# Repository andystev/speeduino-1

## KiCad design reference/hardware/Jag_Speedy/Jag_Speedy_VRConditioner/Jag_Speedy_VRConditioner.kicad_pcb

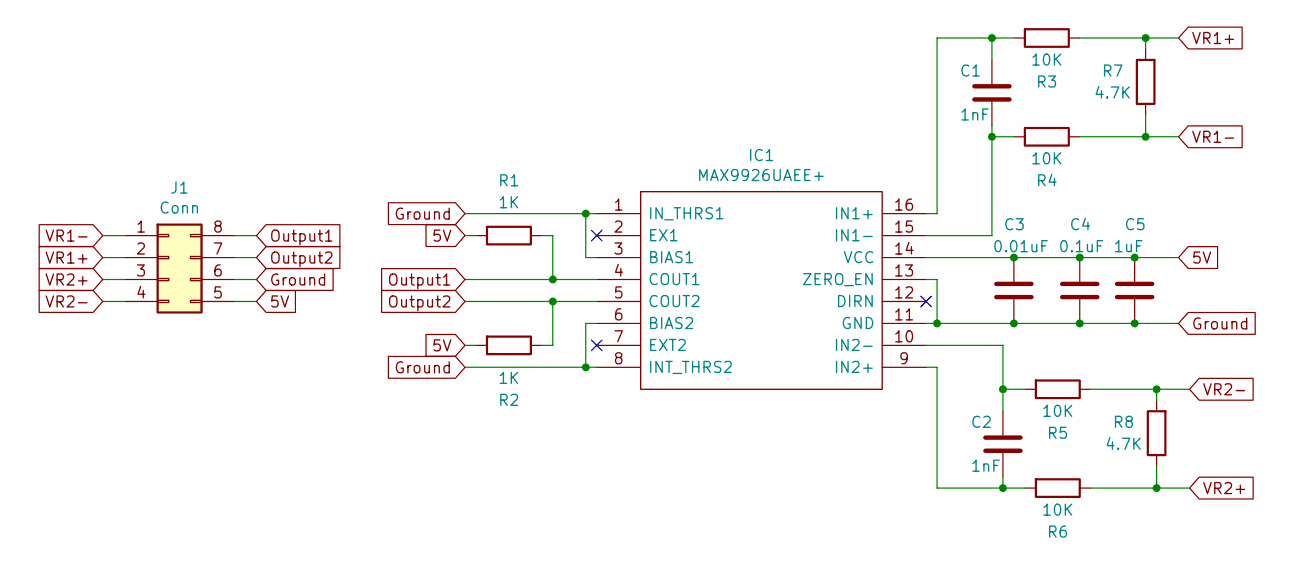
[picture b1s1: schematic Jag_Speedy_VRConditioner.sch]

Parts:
C1, C2: 1nF; C_0805_2012Metric
C3: 0.01uF; C_0805_2012Metric
C4: 0.1uF; C_0805_2012Metric
C5: 1uF; C_0805_2012Metric
IC1: MAX9926UAEE+; QSOP-16_3.9x4.9mm_P0.635mm; Manufacturer_Part_Number MAX9926UAEE+; Mouser Part Number 700-MAX9926UAEE
J1: Conn; DIP-8_W7.62mm_Socket
R1, R2: 1K; R_0805_2012Metric
R3, R4, R5, R6: 10K; R_0805_2012Metric
R7, R8: 4.7K; R_Axial_DIN0411_L9.9mm_D3.6mm_P12.70mm_Horizontal

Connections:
5V: C3.1, C4.1, C5.1, IC1.14 (VCC), J1.5, R1.2, R2.2
Ground: C3.2, C4.2, C5.2, IC1.1 (IN_THRS1), IC1.3 (BIAS1), IC1.6 (BIAS2), IC1.8 (INT_THRS2), IC1.11 (GND), IC1.13 (ZERO_EN), J1.6
unnamed: C1.1, IC1.16 (IN1+), R3.2
unnamed: C1.2, IC1.15 (IN1-), R4.2
unnamed: C2.1, IC1.10 (IN2-), R5.2
unnamed: C2.2, IC1.9 (IN2+), R6.2
Output1: IC1.4 (COUT1), J1.8, R1.1
Output2: IC1.5 (COUT2), J1.7, R2.1
VR1+: J1.2, R3.1, R7.2
VR1-: J1.1, R4.1, R7.1
VR2+: J1.3, R6.1, R8.1
VR2-: J1.4, R5.1, R8.2

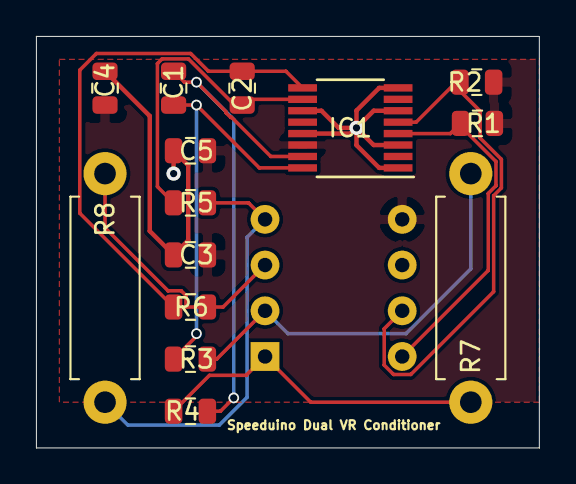
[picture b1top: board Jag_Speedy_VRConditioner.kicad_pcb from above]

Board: 2 copper layers, 27.9 x 22.9 mm, 15 parts (1 on the bottom side), 12 nets.

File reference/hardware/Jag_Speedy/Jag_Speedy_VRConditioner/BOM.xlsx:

QTY Full | Board Reference Full | Value | Type | Information | Manufacturer | Digikey Order | Model# | Digikey P/N | Order Qty | Digikey Price (GBP) | CTM Full Digikey | Order Price (GBP) | Note | Digikey import | General Description
 |  |  |  |  |  |  |  |  |  |  |  |  |  |  | x
2 | R1,R2 | 1k | RES SMD 1K OHM 1% 1/8W 0805 |  | Yageo | Y | RC0805FR-071KL | 311-1.00KCRCT-ND | 10 | 3.2000000000000001E-2 | 6.4000000000000001E-2 | 0.32 |  | 2,311-1.00KCRCT-ND | Resistor - 2x 1k
4 | R3,R4,R5,R6 | 10k | RES SMD 10K OHM 5% 1/8W 0805 |  | Yageo | Y | RC0805JR-0710KL | 311-10KARCT-ND | 20 | 2.7E-2 | 0.108 | 0.54 |  | 4,311-10KARCT-ND | Resistor - 4x 10k
2 | R7,R8 | 4.3k | RES 4.7K OHM 2W 5% AXIAL |  | Yageo | Y | FMP200JR-52-4K7 | 4.7KZCT-ND | 10 | 0.22600000000000001 | 0.45200000000000001 | 2.2600000000000002 |  | 2,4.7KZCT-ND | Resistor - 2x 4.3k
1 | C3 | 0.01uF | CAP CER 10000PF 50V X7R 0805 |  | Yageo | Y | CC0805KRX7R9BB103 | 311-1136-1-ND | 10 | 0.06 | 0.06 | 0.6 |  | 1,311-1136-1-ND | Capacitor - 1x 0.01uF
1 | C5 | 1uF | CAP CER 1UF 16V X7R 0805 |  | Yageo | Y | CC0805KKX7R7BB105 | 311-1365-1-ND | 10 | 0.10100000000000001 | 0.10100000000000001 | 1.01 |  | 1,311-1365-1-ND | Capacitor - 1x 1uF
2 | C1,C2 | 1nF | CAP CER 1000PF 50V X7R 0805 |  | Yageo | Y | CC0805KRX7R9BB102 | 311-1127-1-ND | 10 | 0.06 | 0.12 | 0.6 |  | 2,311-1127-1-ND | Capacitor - 2x 1nF
1 | C4 | 0.1uF | CAP CER 0.1UF 50V Y5V 0805 |  | Yageo | Y | CC0805ZRY5V9BB104 | 311-1361-1-ND | 10 | 0.06 | 0.06 | 0.6 |  | 1,311-1361-1-ND | Capacitor - 1x 0.1uF
 |  |  |  |  |  |  |  |  |  |  |  | 0
 |  |  |  |  |  |  |  |  |  |  |  | 0
1 | IC1 |  | IC SENSOR INTERFACE VARI 16-QSOP | 16-QSOP | Maxim Integrated | Y | MAX9926UAEE+T | MAX9926UAEE+TCT-ND | 5 | 4.32 | 4.32 | 21.6 |  | 1,MAX9926UAEE+TCT-ND | IC- 1x
2 | J1, | 0.100" | 4 Positions Header, Unshrouded, Breakaway Connector 0.100" (2.54mm) Through Hol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 | Pins for board | Harwin Inc | Y | M20-9990445 | 952-2265-ND | 10 | 0.27 | 0.54 | 2.7 |  | 2,952-2265-ND | Pins- 2x 0.100"
1 |  |  |  |  |  |  |  |  |  | 0 | 0 | 0
 |  |  |  |  |  |  | Total of Materials:Cost to Manufacture |  |  | GBP | 5.8250000000000002 | 30.23 | Not including shipping
 |  |  |  |  |  |  |  | Boards | 5 | 5.58 | 1.1160000000000001
 |  |  |  |  |  |  |  | Board Breakdown
 |  |  |  |  |  |  |  | Components + VAT |  |  | 6.99
 |  |  |  |  |  |  |  | Boards |  |  | 1.1160000000000001
 |  |  |  |  |  |  |  | Import Tax etc. |  |  | 0
 |  |  |  |  |  |  |  |  |  |  | 8.1059999999999999

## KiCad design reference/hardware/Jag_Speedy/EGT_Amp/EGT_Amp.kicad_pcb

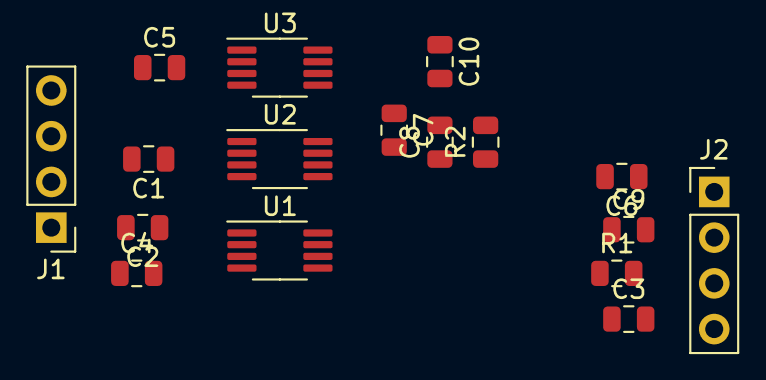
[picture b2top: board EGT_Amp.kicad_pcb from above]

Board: 2 copper layers, 17 parts (0 on the bottom side), 9 nets, no tracks yet.

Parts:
C1, C2, C3, C4, C5, C6, C7, C8, C9, C10: 0.1uF; C_0805_2012Metric
J1: Input; PinHeader_1x04_P2.54mm_Vertical
J2: Output; PinHeader_1x04_P2.54mm_Vertical
R1, R2: 1M; R_0805_2012Metric
U1, U2, U3: AD8495; MSOP-8_3x3mm_P0.65mm

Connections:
+InLeft: C2.2, C3.1, J1.1, R1.1, U1.8
+InRight: C7.2, C8.1, J1.3, R2.1, U2.8
-InLeft: C1.2, C2.1, J1.2, U1.1
-InRight: C6.2, C7.1, J1.4, U2.1
GND: C1.1, C3.2, C4.1, C4.2, C5.2, C6.1, C8.2, C9.1, C9.2, C10.2, J2.3, R1.2, R2.2, U1.2, U1.3, U2.2, U2.3, U3.1, U3.2, U3.3, U3.8
SignalOutAmbient: J2.1, U3.5, U3.6
SignalOutLeft: J2.4, U1.5, U1.6
SignalOutRight: U2.5, U2.6
VSS: C5.1, C10.1, J2.2, U1.7, U2.7, U3.7

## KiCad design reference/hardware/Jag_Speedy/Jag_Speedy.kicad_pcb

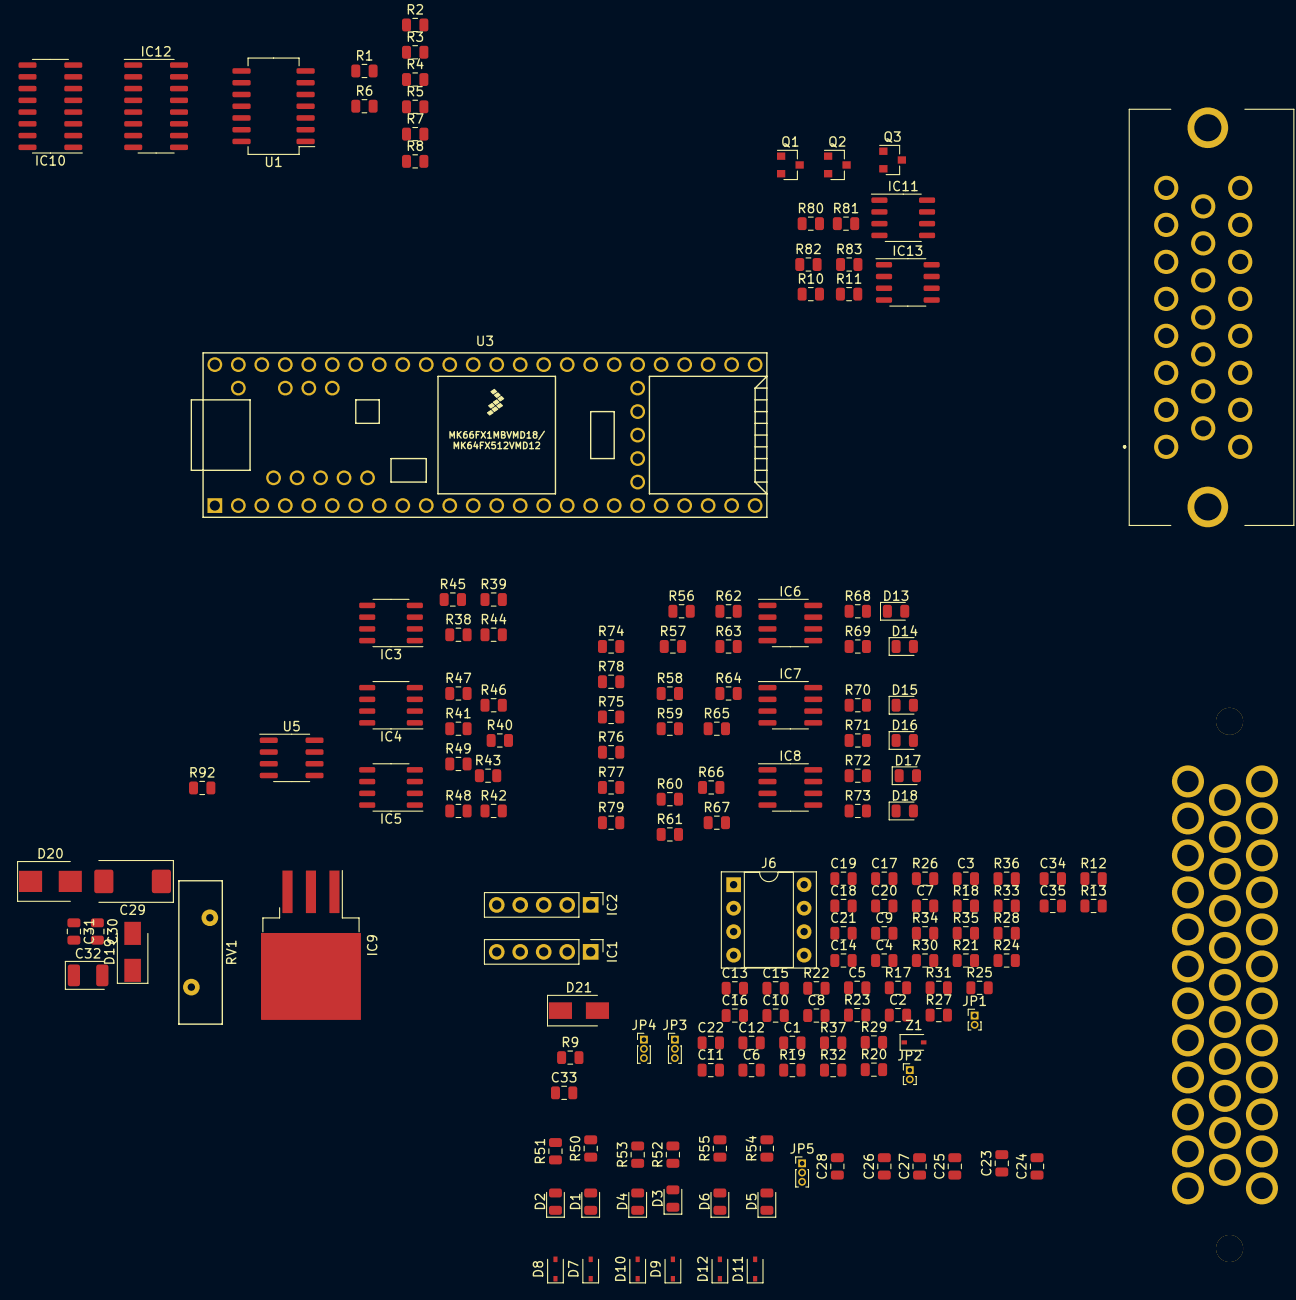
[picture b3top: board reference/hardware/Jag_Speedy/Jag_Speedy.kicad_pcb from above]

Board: 2 copper layers, 166 parts (0 on the bottom side), 132 nets, no tracks yet.

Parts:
C1, C9, C12, C13, C14, C15, C16, C23, C24, C25, C30, C31, C34: 0.1uF; C_0805_2012Metric
C2, C5, C11, C17, C18, C19, C20, C22, C35: 0.22uF; C_0805_2012Metric
C3, C7, C26, C27, C28: 1uF; C_0805_2012Metric
C4, C8: 0.3uF; C_0805_2012Metric
C6, C10, C21: 0.01uF; C_0805_2012Metric
C29: 10uF; CP_EIA-7343-31_Kemet-D
C32: 47uF; CP_EIA-3528-21_Kemet-B
C33: 4.7nF; C_0805_2012Metric
D1, D2, D3, D4, D5, D6, D13, D14, D15, D16, D17, D18: LED; LED_0805_2012Metric
D7, D8, D9, D10, D11, D12: 1N4004; D_SOD-323
D19, D21: 1N5818; D_SMA
D20: 1N5919BG; D_SMB
IC1, IC2: MPX4250AP; PinHeader_1x05_P2.54mm_Vertical
IC3, IC4, IC5, IC11, IC13: VNS3NV04DP-E; SO-8_3.9x4.9mm_P1.27mm
IC6, IC7, IC8: TC4424EPA; SOIC-8_3.9x4.9mm_P1.27mm
IC9: LM2940T-5.0_NOPB; TO-263-3_TabPin2
IC10, IC12: SP720APP; SOIC-16_3.9x9.9mm_P1.27mm
J1: 776087-1; 7760871
J2: 776163-1
J6: Dual VR Conditioner; DIP-8_W7.62mm_Socket
JP1, JP2: Pullup; PinHeader_1x02_P1.00mm_Vertical
JP3, JP4: VR Jumper; PinHeader_1x03_P1.00mm_Vertical
JP5: Ign Source Jumper; PinHeader_1x03_P1.00mm_Vertical
Q1, Q2, Q3: SSM3K357R,LF; SOT-23
R1, R2, R7, R8: 180k; R_0805_2012Metric
R3, R4, R5, R6: 330k; R_0805_2012Metric
R9, R92: 10K; R_0805_2012Metric
R10, R38, R39, R40, R41, R42, R43, R56, R57, R58, R59, R60, R61, R80, R81: 100k; R_0805_2012Metric
R11, R20, R28, R34, R35, R44, R45, R46, R47, R48, R49, R62, R63, R64, R65, R66, R67, R82, R83: 1k; R_0805_2012Metric
R12, R19, R23, R24, R25, R26, R68, R69, R70, R71, R72, R73: 2.49k; R_0805_2012Metric
R13, R18, R22, R29, R30, R31, R32, R33: 470; R_0805_2012Metric
R17, R21: 750; R_0805_2012Metric
R27: 3.9k; R_0805_2012Metric
R36, R37: 220R; R_0805_2012Metric
R50, R51, R52, R53, R54, R55: 680; R_0805_2012Metric
R74, R75, R76, R77, R78, R79: 10R; R_0805_2012Metric
RV1: ERZV14D220; RV_Disc_D15.5mm_W4.7mm_P7.5mm
U1: LMV324; SO-14_5.3x10.2mm_P1.27mm
U3: Teensy 3.5; Teensy35_36
U5: SN65HVD230; SOIC-8_3.9x4.9mm_P1.27mm
Z1: MM3Z5V1ST1G; D_SOD-323

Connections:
3V3: IC12.16, J1.20, J2.1, R12.1, R23.1, R24.1, R25.1, R26.1, U1.4, U3.15, U3.26, U5.3
5V: C3.1, C6.1, C7.1, C10.1, C31.1, C32.1, D20.1, D21.1, IC1.3, IC2.3, IC9.3, IC10.16, J1.11, J1.19, J2.18, J6.5, JP5.3, R9.1, R19.2, R34.2, R35.1, U3.53
12V: D19.2, J1.14, JP5.1, R27.1, R50.1, R51.1, R52.1, R53.1, R54.1, R55.1, RV1.1
ADCClamp01: C21.2, IC10.1, J6.8, R36.2, U3.50
ADCClamp02: C22.1, IC10.2, J6.7, R37.2, U3.33
ADCClamp03: C5.1, IC10.3, R7.2, R18.2
ADCClamp04: C11.1, IC10.4, R8.2, R22.2
ADCClamp05: IC12.1, R33.2, U3.45
ADCClamp06: C4.2, IC10.6, R1.1, R17.2
ADCClamp07: C8.2, IC10.7, R2.1, R21.2
ADCClamp08: C17.1, IC10.5, R29.2, U3.41
ADCClamp09: C18.1, IC12.9, R30.2, U3.42
ADCClamp10: C19.1, IC12.3, R31.2, U3.56
ADCClamp11: C20.1, C35.1, IC12.2, R13.2, R32.2, U3.47, U3.57
Barro-Signal-3.3V: U1.6, U1.7, U3.46
BluetoothRx: J1.22, U3.3
BluetoothTx: J1.23, U3.2
CAN-Rx: U3.6, U5.4
CAN-Tx: U3.5, U5.1
CANH: J1.15, U5.7
CANL: J1.16, U5.6
CCPump-OUT: IC11.5, J1.2
CCPump-Signal: R81.1, R83.1, U3.21
CLTSensor: C13.1, J2.8, R24.2, R30.1
CPU-A2: U1.8, U1.9, U3.43
CPU-A3: U1.13, U1.14, U3.44
CPU-A8: U1.1, U1.2, U3.49
CPU-D05: R80.2, R82.1, U3.7
CPU-D08: R38.2, R44.1, U3.10
CPU-D09: R39.1, R45.1, U3.11
CPU-D10: R40.1, R46.1, U3.12
CPU-D11: R41.1, R47.1, U3.13
CPU-D12: R42.2, R48.1, U3.14
CPU-D13: R43.1, R49.1, U3.40
CPU-D21: R59.1, R65.1, U3.48
CPU-D24: R20.2, U3.16, Z1.1
CPU-D25: C2.1, J2.2, R19.1, U3.17
CPU-D27: Q1.1, U3.19
CPU-D28: Q3.1, U3.20
CPU-D30: R10.2, R11.1, U3.22
CPU-D31: R58.2, R64.1, U3.23
CPU-D32: R60.2, R66.1, U3.24
CPU-D35: R61.1, R67.1, U3.32
CPU-D37: Q2.1, U3.34
CPU-D38: R57.1, R63.1, U3.35
CPU-D39: R56.2, R62.1, U3.36
CamSensor+: J2.16, JP2.2, JP4.2
CamSensor-: J2.17, J6.4
ClutchSwitch: J2.21, R20.1
CrankSensor+: J2.14, JP1.2, JP3.2
CrankSensor-: J2.15, J6.1
EGRSensor: C34.1, J2.12, R12.2, R13.1
Fan-OUT: J1.5, Q1.2
FuelPressureSensor: C14.1, J2.19, R25.2, R31.1
FuelPump-OUT: J1.4, Q2.2
IATSensor: C12.1, J2.6, R23.2, R29.1
IdlePWM-OUT: IC11.7, J1.6
Ign01-OUT: J2.29, R74.2
Ign02-OUT: J2.30, R75.2
Ign03-OUT: J2.31, R76.2
Ign04-OUT: J2.32, R77.2
Ign05-OUT: J2.33, R78.2
Ign06-OUT: J2.34, R79.2
IgnSourceV: C23.1, C24.1, C25.1, C26.1, C27.1, C28.1, IC6.6, IC7.6, IC8.6, JP5.2
Inj01-OUT: D7.1, IC3.7, J2.23
Inj02-OUT: D8.1, IC3.5, J2.24
Inj03-OUT: D9.1, IC4.7, J2.25
Inj04-OUT: D10.1, IC4.5, J2.26
Inj05-OUT: D11.1, IC5.7, J2.27
Inj06-OUT: D12.1, IC5.5, J2.28
unnamed: C16.1, R27.2, R28.1, R33.1
unnamed: C29.1, C30.1, D19.1, IC9.1
unnamed: D1.1, D7.2
unnamed: D1.2, R50.2
unnamed: D2.1, D8.2
unnamed: D2.2, R51.2
unnamed: D3.1, D9.2
unnamed: D3.2, R52.2
unnamed: D4.2, R53.2
unnamed: D5.2, R54.2
unnamed: D6.2, R55.2
unnamed: D4.1, D10.2
unnamed: D5.1, D11.2
unnamed: D6.1, D12.2
unnamed: D13.2, R68.1
unnamed: D14.2, R69.1
unnamed: D15.2, R70.1
unnamed: D16.2, R71.1
unnamed: D17.2, R72.1
unnamed: D18.2, R73.1
unnamed: IC1.1, R17.1
unnamed: IC2.1, R21.1
unnamed: IC3.2, R44.2
unnamed: IC3.4, R45.2
unnamed: IC4.2, R46.2
unnamed: IC4.4, R47.2
unnamed: IC5.2, R48.2
unnamed: IC5.4, R49.2
unnamed: IC6.2, R62.2
unnamed: IC6.4, R63.2
unnamed: IC6.5, R69.2, R75.1
unnamed: IC6.7, R68.2, R74.1
unnamed: IC7.2, R64.2
unnamed: IC7.4, R65.2
unnamed: IC7.5, R71.2, R77.1
unnamed: IC7.7, R70.2, R76.1
unnamed: IC8.2, R66.2
unnamed: IC8.4, R67.2
unnamed: IC8.5, R73.2, R79.1
unnamed: IC8.7, R72.2, R78.1
unnamed: IC11.2, R82.2
unnamed: IC11.4, R83.2
unnamed: IC13.2, R11.2
unnamed: J6.2, JP3.3
unnamed: J6.3, JP4.3
unnamed: JP1.1, R34.1
unnamed: JP2.1, R35.2
unnamed: JP3.1, R36.1
unnamed: JP4.1, R37.1
unnamed: R1.2, R4.1, U1.12
unnamed: R2.2, R3.1, U1.5
unnamed: R5.2, R7.1, U1.3
unnamed: R6.2, R8.1, U1.10
unnamed: R92.1, U5.8
O2Sensor: C1.1, J2.10, R18.1
OilPressureSensor: C15.1, J2.20, R26.2, R32.1
PowerGnd: C23.2, C24.2, C25.2, C26.2, C27.2, C28.2, C29.2, C30.2, C31.2, C32.2, C33.2, D13.1, D14.1, D15.1, D16.1, D17.1, D18.1, D20.2, IC3.1, IC3.3, IC4.1, IC4.3, IC5.1, IC5.3, IC6.3, IC7.3, IC8.3, IC9.2, IC10.8, IC11.1, IC11.3, IC12.8, IC13.1, IC13.3, J1.3, J1.9, J1.10, J1.17, J1.18, J1.21, J2.3, J2.5, J2.7, J2.9, J2.11, J2.13, J2.22, J2.35, Q1.3, Q2.3, Q3.3, R3.2, R4.2, R5.1, R6.1, R10.1, R38.1, R39.2, R40.2, R41.2, R42.1, R43.2, R56.1, R57.2, R58.1, R59.2, R60.1, R61.2, R80.1, R81.2, R92.2, RV1.2, U1.11, U3.1, U3.27, U3.39, U3.52, U3.60, U3.61, U5.2
Reset: C33.1, D21.2, R9.2, U3.29
SensorGnd: C1.2, C2.2, C3.2, C4.1, C5.2, C6.2, C7.2, C8.1, C9.2, C10.2, C11.2, C12.2, C13.2, C14.2, C15.2, C16.2, C17.2, C18.2, C19.2, C20.2, C21.1, C22.2, C34.2, C35.2, IC1.2, IC2.2, J6.6, R28.2, Z1.2
TPSSensor: C9.1, J2.4, R22.1
Tacho-OUT: J1.8, Q3.2
WPPWM-OUT: IC13.7, J1.12

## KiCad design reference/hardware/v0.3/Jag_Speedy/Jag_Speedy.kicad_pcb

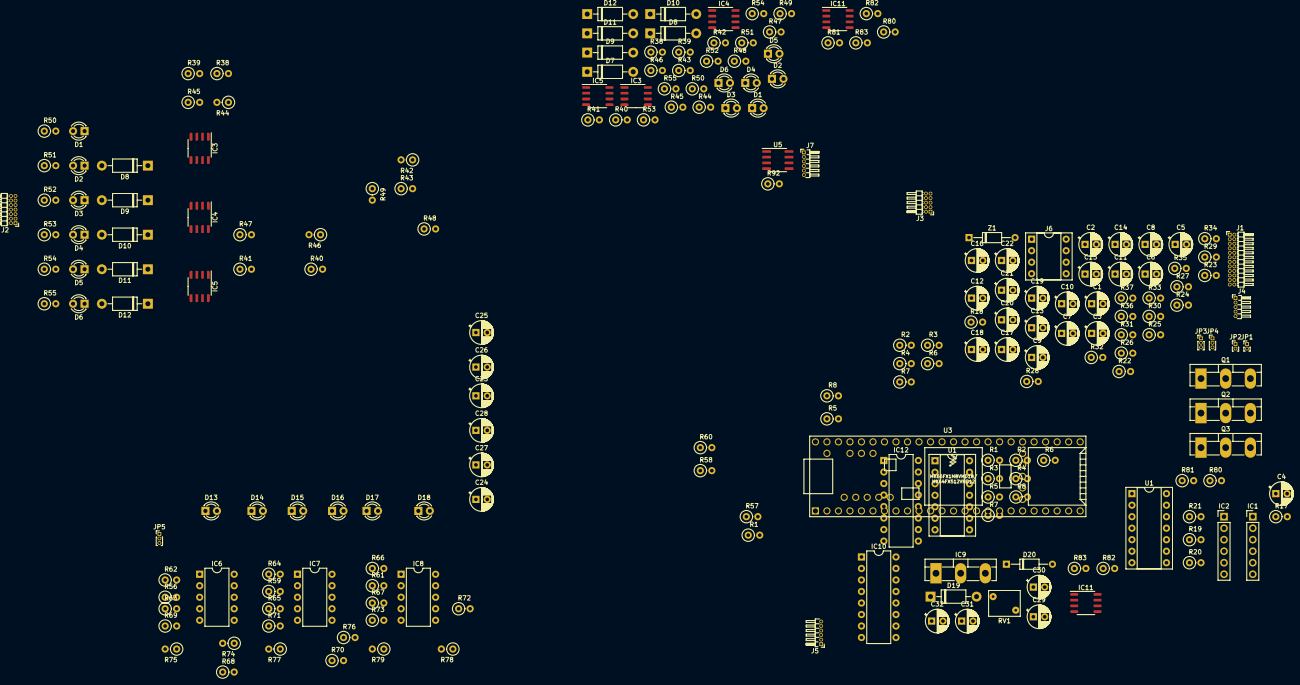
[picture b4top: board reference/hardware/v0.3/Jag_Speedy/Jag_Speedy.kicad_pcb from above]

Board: 2 copper layers, 206 parts (0 on the bottom side), 135 nets, no tracks yet.

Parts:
C1, C9, C12, C13, C14, C15, C16, C23, C24, C25, C30, C31: 0.1uF; CP_Radial_D5.0mm_P2.50mm
C2, C5, C11, C17, C18, C19, C20, C22: 0.22uF; CP_Radial_D5.0mm_P2.50mm
C3, C7, C26, C27, C28: 1uF; CP_Radial_D5.0mm_P2.50mm
C4, C8: 0.3uF; CP_Radial_D5.0mm_P2.50mm
C6, C10, C21: 0.01uF; CP_Radial_D5.0mm_P2.50mm
C29: 10uF; CP_Radial_D5.0mm_P2.50mm
C32: 47uF; CP_Radial_D5.0mm_P2.50mm
D1, D1#2, D2, D2#2, D3, D3#2, D4, D4#2, D5, D5#2, D6, D6#2, D13, D14, D15, D16, D17, D18: LED; LED_D3.0mm
D7, D8, D8#2, D9, D9#2, D10, D10#2, D11, D11#2, D12, D12#2: 1N4004; D_DO-41_SOD81_P10.16mm_Horizontal
D19: 1N5818; D_DO-41_SOD81_P10.16mm_Horizontal
D20: 1N5919BG; D_DO-35_SOD27_P10.16mm_Horizontal
IC1, IC2: MPX4250AP; PinHeader_1x06_P2.54mm_Vertical
IC3, IC3#2, IC4, IC4#2, IC5, IC5#2, IC11, IC11#2: VNS3NV04DP-E; SO-8_3.9x4.9mm_P1.27mm
IC6, IC7, IC8: TC4424EPA; DIP-10_W7.62mm
IC9: LM2940T-5.0_NOPB; TO-3P-3_Vertical
IC10, IC12: SP720APP; DIP-16_W7.62mm
J1: Inputs; PinHeader_2x12_P1.00mm_Horizontal
J2: Ouputs01; PinHeader_2x07_P1.00mm_Horizontal
J3: Outputs02; PinHeader_2x05_P1.00mm_Horizontal
J4: Power; PinHeader_1x05_P1.00mm_Horizontal
J5: Bluetooth; PinHeader_1x06_P1.00mm_Horizontal
J6: Dual VR Conditioner; DIP-8_W7.62mm_Socket
J7: Canbus; PinHeader_1x06_P1.00mm_Horizontal
JP1, JP2: Pullup; PinHeader_1x02_P1.00mm_Vertical
JP3, JP4: VR Jumper; PinHeader_1x03_P1.00mm_Vertical
JP5: Ign Source Jumper; PinHeader_1x03_P1.00mm_Vertical
Q1, Q2, Q3: SSM3K357R,LF; TO-3P-3_Vertical
R1, R1#2, R2, R2#2, R7, R7#2, R8, R8#2: 180k; R_Axial_DIN0207_L6.3mm_D2.5mm_P2.54mm_Vertical
R3, R3#2, R4, R4#2, R5, R5#2, R6, R6#2: 330k; R_Axial_DIN0207_L6.3mm_D2.5mm_P2.54mm_Vertical
R17, R21: 750; R_Axial_DIN0207_L6.3mm_D2.5mm_P2.54mm_Vertical
R18, R22, R29, R30, R31, R32, R33: 470; R_Axial_DIN0207_L6.3mm_D2.5mm_P2.54mm_Vertical
R19, R23, R24, R25, R26, R68, R69, R70, R71, R72, R73: 2.49k; R_Axial_DIN0207_L6.3mm_D2.5mm_P2.54mm_Vertical
R20, R28, R34, R35, R44, R44#2, R45, R45#2, R46, R46#2, R47, R47#2, R48, R48#2, R49, R49#2, R62, R63, R64, R65, R66, R67, R82, R82#2, R83, R83#2: 1k; R_Axial_DIN0207_L6.3mm_D2.5mm_P2.54mm_Vertical
R27: 3.9k; R_Axial_DIN0207_L6.3mm_D2.5mm_P2.54mm_Vertical
R36, R37: 220R; R_Axial_DIN0207_L6.3mm_D2.5mm_P2.54mm_Vertical
R38, R38#2, R39, R39#2, R40, R40#2, R41, R41#2, R42, R42#2, R43, R43#2, R56, R57, R58, R59, R60, R61, R80, R80#2, R81, R81#2: 100k; R_Axial_DIN0207_L6.3mm_D2.5mm_P2.54mm_Vertical
R50, R50#2, R51, R51#2, R52, R52#2, R53, R53#2, R54, R54#2, R55, R55#2: 680; R_Axial_DIN0207_L6.3mm_D2.5mm_P2.54mm_Vertical
R74, R75, R76, R77, R78, R79: 10R; R_Axial_DIN0207_L6.3mm_D2.5mm_P2.54mm_Vertical
R92: 10K; R_Axial_DIN0207_L6.3mm_D2.5mm_P2.54mm_Vertical
RV1: ERZV14D220; RV_Disc_D7mm_W5.7mm_P5mm
U1, U1#2: LMV324; DIP-14_W7.62mm_Socket
U3: Teensy 3.5; Teensy35_36
U5: SN65HVD230; SOIC-8_3.9x4.9mm_P1.27mm
Z1: MM3Z5V1ST1G; D_DO-35_SOD27_P10.16mm_Horizontal

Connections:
3V3: IC12.16, J1.1, J1.12, J4.1, R23.1, R24.1, R25.1, R26.1, U1.4, U1#2.4, U3.15, U3.26, U5.3
5V: C3.1, C6.1, C7.1, C10.1, C31.1, C32.1, D20.1, IC1.3, IC2.3, IC9.3, IC10.16, J1.18, J4.2, J5.2, J6.5, JP5.3, R19.2, R34.2, R35.1, U3.53
12V: D19.2, J4.5, JP5.1, R27.1, R50.1, R50#2.1, R51.1, R51#2.1, R52.1, R52#2.1, R53.1, R53#2.1, R54.1, R54#2.1, R55.1, R55#2.1, RV1.1
ADCClamp01: C21.2, IC10.1, J6.8, R36.2, U3.50
ADCClamp02: C22.1, IC10.2, J6.7, R37.2, U3.33
ADCClamp03: C5.1, IC10.3, R7.2, R7#2.2, R18.2
ADCClamp04: C11.1, IC10.4, R8.2, R8#2.2, R22.2
ADCClamp05: IC12.1, R33.2, U3.45
ADCClamp06: C4.2, IC10.6, R1.1, R1#2.1, R17.2
ADCClamp07: C8.2, IC10.7, R2.1, R2#2.1, R21.2
ADCClamp08: C17.1, IC10.9, R29.2, U3.41
ADCClamp09: C18.1, IC12.9, R30.2, U3.42
ADCClamp10: C19.1, IC12.10, R31.2, U3.56
ADCClamp11: C20.1, IC12.11, R32.2, U3.57
Barro-Signal-3.3V: U1.6, U1.7, U1#2.6, U1#2.7, U3.46
BluetoothRx: J5.4, U3.3
BluetoothTx: J5.3, U3.2
CAN-Rx: U3.6, U5.4
CAN-Tx: U3.5, U5.1
CCPump-OUT: IC11.5, IC11#2.5, J3.2
CCPump-Signal: R81.1, R81#2.1, R83.1, R83#2.1, U3.21
CLTSensor: C13.1, J1.8, R24.2, R30.1
CPU-A2: U1.8, U1.9, U1#2.8, U1#2.9, U3.43
CPU-A3: U1.13, U1.14, U1#2.13, U1#2.14, U3.44
CPU-A8: U1.1, U1.2, U1#2.1, U1#2.2, U3.49
CPU-D05: R80.2, R80#2.2, R82.1, R82#2.1, U3.7
CPU-D08: R38.2, R38#2.2, R44.1, R44#2.1, U3.10
CPU-D09: R39.1, R39#2.1, R45.1, R45#2.1, U3.11
CPU-D10: R40.1, R40#2.1, R46.1, R46#2.1, U3.12
CPU-D11: R41.1, R41#2.1, R47.1, R47#2.1, U3.13
CPU-D12: R42.2, R42#2.2, R48.1, R48#2.1, U3.14
CPU-D13: R43.1, R43#2.1, R49.1, R49#2.1, U3.40
CPU-D21: R59.1, R65.1, U3.48
CPU-D24: R20.2, U3.16, Z1.1
CPU-D25: C2.1, J1.2, R19.1, U3.17
CPU-D27: Q1.1, U3.19
CPU-D28: Q3.1, U3.20
CPU-D31: R58.2, R64.1, U3.23
CPU-D32: R60.2, R66.1, U3.24
CPU-D35: R61.1, R67.1, U3.32
CPU-D37: Q2.1, U3.34
CPU-D38: R57.1, R63.1, U3.35
CPU-D39: R56.2, R62.1, U3.36
CamSensor+: J1.16, JP2.2, JP4.2
CamSensor-: J1.17, J6.4
ClutchSwitch: J1.23, R20.1
CrankSensor+: J1.14, JP1.2, JP3.2
CrankSensor-: J1.15, J6.1
Fan-OUT: J3.5, Q1.2
FuelPressureSensor: C14.1, J1.19, R25.2, R31.1
FuelPump-OUT: J3.4, Q2.2
IATSensor: C12.1, J1.6, R23.2, R29.1
IdlePWM-OUT: IC11.7, IC11#2.7, J3.6
Ign01-OUT: J2.8, R74.2
Ign02-OUT: J2.9, R75.2
Ign03-OUT: J2.10, R76.2
Ign04-OUT: J2.11, R77.2
Ign05-OUT: J2.12, R78.2
Ign06-OUT: J2.13, R79.2
IgnSourceV: C23.1, C24.1, C25.1, C26.1, C27.1, C28.1, IC6.6, IC7.6, IC8.6, JP5.2
Inj01-OUT: D7.1, IC3.7, IC3#2.7, J2.2
Inj02-OUT: D8.1, D8#2.1, IC3.5, IC3#2.5, J2.3
Inj03-OUT: D9.1, D9#2.1, IC4.7, IC4#2.7, J2.4
Inj04-OUT: D10.1, D10#2.1, IC4.5, IC4#2.5, J2.5
Inj05-OUT: D11.1, D11#2.1, IC5.7, IC5#2.7, J2.6
Inj06-OUT: D12.1, D12#2.1, IC5.5, IC5#2.5, J2.7
unnamed: C16.1, R27.2, R28.1, R33.1
unnamed: C29.1, C30.1, D19.1, IC9.1
unnamed: D1.1, D1#2.1, D7.2
unnamed: D1.2, D1#2.2, R50.2, R50#2.2
unnamed: D2.1, D2#2.1, D8.2, D8#2.2
unnamed: D2.2, D2#2.2, R51.2, R51#2.2
unnamed: D3.1, D3#2.1, D9.2, D9#2.2
unnamed: D3.2, D3#2.2, R52.2, R52#2.2
unnamed: D4.2, D4#2.2, R53.2, R53#2.2
unnamed: D5.2, D5#2.2, R54.2, R54#2.2
unnamed: D6.2, D6#2.2, R55.2, R55#2.2
unnamed: D4.1, D4#2.1, D10.2, D10#2.2
unnamed: D5.1, D5#2.1, D11.2, D11#2.2
unnamed: D6.1, D6#2.1, D12.2, D12#2.2
unnamed: D13.2, R68.1
unnamed: D14.2, R69.1
unnamed: D15.2, R70.1
unnamed: D16.2, R71.1
unnamed: D17.2, R72.1
unnamed: D18.2, R73.1
unnamed: IC1.1, R17.1
unnamed: IC2.1, R21.1
unnamed: IC3.2, IC3#2.2, R44.2, R44#2.2
unnamed: IC3.4, IC3#2.4, R45.2, R45#2.2
unnamed: IC3.6, IC3#2.6
unnamed: IC3.8, IC3#2.8
unnamed: IC4.2, IC4#2.2, R46.2, R46#2.2
unnamed: IC4.4, IC4#2.4, R47.2, R47#2.2
unnamed: IC4.6, IC4#2.6
unnamed: IC4.8, IC4#2.8
unnamed: IC5.2, IC5#2.2, R48.2, R48#2.2
unnamed: IC5.4, IC5#2.4, R49.2, R49#2.2
unnamed: IC5.6, IC5#2.6
unnamed: IC5.8, IC5#2.8
unnamed: IC6.2, R62.2
unnamed: IC6.4, R63.2
unnamed: IC6.5, R69.2, R75.1
unnamed: IC6.7, R68.2, R74.1
unnamed: IC7.2, R64.2
unnamed: IC7.4, R65.2
unnamed: IC7.5, R71.2, R77.1
unnamed: IC7.7, R70.2, R76.1
unnamed: IC8.2, R66.2
unnamed: IC8.4, R67.2
unnamed: IC8.5, R73.2, R79.1
unnamed: IC8.7, R72.2, R78.1
unnamed: IC11.2, IC11#2.2, R82.2, R82#2.2
unnamed: IC11.4, IC11#2.4, R83.2, R83#2.2
unnamed: IC11.6, IC11#2.6
unnamed: IC11.8, IC11#2.8
unnamed: J6.2, JP3.3
unnamed: J6.3, JP4.3
unnamed: J7.1, U5.7
unnamed: J7.2, U5.6
unnamed: JP1.1, R34.1
unnamed: JP2.1, R35.2
unnamed: JP3.1, R36.1
unnamed: JP4.1, R37.1
unnamed: R1.2, R1#2.2, R4.1, R4#2.1, U1.12, U1#2.12
unnamed: R2.2, R2#2.2, R3.1, R3#2.1, U1.5, U1#2.5
unnamed: R5.2, R5#2.2, R7.1, R7#2.1, U1.3, U1#2.3
unnamed: R6.2, R6#2.2, R8.1, R8#2.1, U1.10, U1#2.10
unnamed: R92.1, U5.8
O2Sensor: C1.1, J1.10, R18.1
OilPressureSensor: C15.1, J1.21, R26.2, R32.1
PowerGnd: C23.2, C24.2, C25.2, C26.2, C27.2, C28.2, C29.2, C30.2, C31.2, C32.2, D13.1, D14.1, D15.1, D16.1, D17.1, D18.1, D20.2, IC3.1, IC3.3, IC3#2.1, IC3#2.3, IC4.1, IC4.3, IC4#2.1, IC4#2.3, IC5.1, IC5.3, IC5#2.1, IC5#2.3, IC6.3, IC7.3, IC8.3, IC9.2, IC10.8, IC11.1, IC11.3, IC11#2.1, IC11#2.3, IC12.8, J1.3, J1.5, J1.7, J1.9, J1.11, J1.13, J1.20, J1.22, J1.24, J2.1, J2.14, J3.3, J3.9, J3.10, J4.3, J4.4, J5.1, Q1.3, Q2.3, Q3.3, R3.2, R3#2.2, R4.2, R4#2.2, R5.1, R5#2.1, R6.1, R6#2.1, R38.1, R38#2.1, R39.2, R39#2.2, R40.2, R40#2.2, R41.2, R41#2.2, R42.1, R42#2.1, R43.2, R43#2.2, R56.1, R57.2, R58.1, R59.2, R60.1, R61.2, R80.1, R80#2.1, R81.2, R81#2.2, R92.2, RV1.2, U1.11, U1#2.11, U3.1, U3.27, U3.39, U3.52, U3.60, U3.61, U5.2
SensorGnd: C1.2, C2.2, C3.2, C4.1, C5.2, C6.2, C7.2, C8.1, C9.2, C10.2, C11.2, C12.2, C13.2, C14.2, C15.2, C16.2, C17.2, C18.2, C19.2, C20.2, C21.1, C22.2, IC1.2, IC2.2, J6.6, R28.2, Z1.2
TPSSensor: C9.1, J1.4, R22.1
Tacho-OUT: J3.8, Q3.2

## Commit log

2020-06-27 KiCad update
2020-06-29 Schematic pin mapping
2020-06-29 Canbus Tranceiver
2020-06-29 Driver replacement
2020-06-29 MOSFET Drivers
2020-06-30 Rationalise level shifting
2020-06-30 Schematic tidyup
2020-06-30 PCB Update
2020-07-01 SMD Update
2020-07-02 VR Conditioner
2020-07-02 VR PCB
2020-07-03 VR Cond PCB update
2020-07-07 VR PCB Update
2020-07-07 Ground & Pwer Planes
2020-07-08 PCB Connector Fix
2020-07-08 PCB Changes
2020-07-12 PCB Updates
2020-07-15 PCB Rework
2020-07-15 Text update
2020-07-15 Tweaks
2020-07-16 VR Gerbers & BOM
2020-07-20 Connector update
2020-07-24 PCB Connectors
2020-07-27 Added Water Pump PWM
2020-07-29 EGR Input
2020-07-31 EGT Amp
2020-10-30 final
2020-12-20 pcb tweaks
